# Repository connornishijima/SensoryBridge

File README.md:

https://github.com/connornishijima/SensoryBridge/assets/5051485/211737f4-0c69-49b0-99c4-2fa3d6a7a65e

# SENSORY BRIDGE is **DIFFERENT**

**This isn't the usual "sound-reactive LEDs" you've seen for years.**

**Sensory Bridge is built from the ground up as an open, powerful bridge between sight and sound.** With a show that's reactive to notation, vibrato and more, it produces very unique and pleasant-to-look-at light shows which synchronize to your music without any visible latency. (A built-in MEMS microphone constantly studies what it hears using a special-sauce Goertzel-based Discrete Fourier Transform, at 100 FPS!)

It has to be seen to be believed, *which the video demos below can help with:*

# 

# SENSORY BRIDGE is **SIMPLE**

**Easy controls provide quick access to changing the brightness, color, and smoothing of the display!**

# **KNOBS**

## PHOTONS KNOB

Too bright? *Dim down the show* with the **PHOTONS** knob. The FastLED code in the firmware will use dithering to keep producing color nicely at lower brightness levels.

## CHROMA KNOB

Custom color or automated color based on the music's notation? Choose with the **CHROMA** knob, where turning it all the way to the top enables automated color changes.

## MOOD KNOB

This knob is special. **MOOD** controls *how quickly your LEDs will react to changes in pitch and volume!* A low "mood" will be very soft and gradual, only showing things like the underlying chord progression of a song, whereas a *high* "mood" will be extremely reactive, and can be a little too flashy for some people's liking. Luckily, you can blend the value to anywhere between those two extremes whenever you want to find what look you prefer!

# 

# **BUTTONS**

## NOISE BUTTON

Running the A/C? Is the washing machine suddenly on the spin cycle? Don't worry, just pause the music for a moment and press the **NOISE BUTTON** to run a 3-second calibration to *automagically* have noisy background ambience removed from your light show.

## MODE BUTTON

Sensory Bridge currently has 6 built-in light show modes that you can cycle through:

### "Spectrogram Mode"

This is the default show seen in the videos, based on Discrete Fourier Transform data. Each octave of notation shown on the display has a spectrum of colors for the individual notes, which are lit in sync with your music!

### "Chromagram Mode"

Similar to Spectrogram Mode, but all octaves of notes are rolled into one! Best with the **MOOD** knob at a low to medium setting.

### "Bloom Mode"

This mode differs from the others. The intensity of the audio is shown in the center of the LED strip, and is diffused outward in a non-linear fashion as time passes, leading to a 2001 "Stargate Sequence" effect!. Color is derived from the notes your music is playing.

### "Bloom Mode" (Faster)

Same as above, but double the speed for when you're partying hard!

### "VU Meter Mode"

It's a classic! A bouncing bar graph represents the current loudness of the music.

### "VU Meter Mode (Dot)"

Same as above, but represented with a dot instead of a bar, staying a constant brightness.

## ***MORE MODES WILL BE RELEASED IN FUTURE FIRMWARE UPDATES!***

# 

# **SWEET SPOT**

At the front of the base unit are three LEDs, which indicate if your music is playing too quietly for the auto-ranger to account for, or if it's too loud! (Close to clipping!)

# 

# SENSORY BRIDGE is **FLEXIBLE**

While compatible with any WS2812B or APA102/SK9822-based LED strip (just use the screw terminals at the back!) there's also the option of using the **"Mini Mast"**, a dense strip of 128 1.5mm RGB LEDs on a 260mm long PCB! It just plugs directly into the Sensory Bridge accessory port, making for a very portable solution!

# 

# SENSORY BRIDGE is **OPEN**

--------------------------------------------------------

### NOTE: This repo is used for active development.

For the latest stable release of the Sensory Bridge firmware, **[visit the Releases page](https://github.com/connornishijima/SensoryBridge/releases)**! (Cloning straight from this repo is much like a "nightly" build, and may be broken code!)

--------------------------------------------------------

Powered by an ESP32-S2, Sensory Bridge can be easily reprogrammed for any purpose you'd like! The firmware is [open source](https://github.com/connornishijima/SensoryBridge) under the [MIT License](https://github.com/connornishijima/SensoryBridge/blob/main/LICENSE), so modifying it for your own purposes is quick and easy with the Arduino IDE. You can even download the [board](https://github.com/connornishijima/SensoryBridge/tree/main/extras/OSHW/PCB) and [case STLs](https://github.com/connornishijima/SensoryBridge/tree/main/extras/OSHW/3D%20Printing) to build one yourself!

# 

# WHAT'S **INCLUDED:**

For $50, you'll receive a ***fully assembled Sensory Bridge***, with the latest firmware already installed. For $25 extra, you can have a **Mini Mast** (128 micro-LED PCB, seen above) sent as well, with an accompanying brace that provides rigidity. (It just plugs right into the accessory port on top of Sensory Bridge!)

# EXTRAS YOU **MIGHT NEED:**

## **PAY CLOSE ATTENTION TO THIS SECTION!**

To save on redundant materials you might already own, **your Sensory Bridge does *not* come with the following items:**

- **WS2812B LED Strip** - "144-LEDs per meter" variants are recommended, you can cut the 16 excess LEDs off of the end of the strip or reconfigure your device to interpolate to the 144-LED length at a slightly lower frame rate. ([AMAZON LINK](https://www.amazon.com/WS2812B-Individual-Addressable-144Pixels-Non-Waterproof/dp/B09PBHJG6G/ref=sr_1_5?crid=3KPXUN3NEV06Q&keywords=ws2812b%2Bled%2Bstrip%2B144&qid=1662389723&sprefix=ws2812b%2Bled%2Bstrip%2B144%2Caps%2C128&sr=8-5&th=1))
- **USB-C Cable** ([AMAZON LINK](https://www.amazon.com/JSAUX-Charger-Braided-Compatible-Samsung/dp/B076FPGWNZ/ref=sr_1_9?crid=2YG0J3B874G73&keywords=usb-c+cable&qid=1662388265&sprefix=usb-c+cable%2Caps%2C137&sr=8-9))
- **5V, 2A USB Power Adapter** ([AMAZON LINK](https://www.amazon.com/Certified-Charger-FONKEN-Universal-Compatible/dp/B07DF782WQ/ref=sr_1_4?crid=1WJDP9XHVR3QC&keywords=2a+usb+adapter&qid=1662388344&sprefix=2a+usb+adapter%2Caps%2C131&sr=8-4))
- **Wire Stripper** - If you'd like to use your Sensory Bridge with your own LED strip, you'll either need a wire stripper or strong teeth to get it hooked up neatly! These clamp-style strippers make that process a breeze, so please don't use your teeth: ([AMAZON LINK](https://www.amazon.com/Self-Adjusting-Stripper-Klein-Tools-11061/dp/B00CXKOEQ6/ref=sr_1_5?crid=UIAP8SCLPER3&keywords=wire+strippers&qid=1662390513&sprefix=wire+strippers%2Caps%2C141&sr=8-5))

# 

# FUTURE **PLANS**

Sensory Bridge is going to undergo some upgrades in the following months! You'll be able to easily [update to the latest firmware in minutes with this guide](DEAD LINK).

**Currently planned features are:**

## WiFi Features

Planned for Q1 2023 is a mobile / web app for iOS and Android that will allow users to remotely tweak their display from the couch! This will provide a way to adjust dozens of settings that otherwise couldn't be accessed through just two physical buttons.

## More Lightshow Modes

Currently in development is a system of determining and synchronizing to the BPM of the playing music. Combining this data with the GDFT could mean deducing time signatures, along with musical keys and chord progressions - just another avenue for providing an immersive show!

## Support For Line-In Audio

The accessory port exposes GPIO 17/18 of the ESP32-S2, which are analog inputs. In the future, a PCB can be made to allow Sensory Bridge to use hardwired, passthrough audio via two 3.5mm jacks. This concept does not interfere with the Mini Mast, and the two accessories will be stackable with a modified brace.

# **GETTING STARTED**

The **[GETTING STARTED](https://sensorybridge.rocks/tutorial/) GUIDE** will walk you through the quick-and-easy setup process!

# **DISCLAIMER**

## **Those with [Photosensitive Epilepsy](https://en.wikipedia.org/wiki/Photosensitive_epilepsy) (PSE) should NOT purchase, operate, or otherwise view Sensory Bridge under any condition.**

## **The seller assumes no legal liability for injury caused to persons with PSE that have ignored this warning.**

# **SPONSORS**

- **[mlctrez](https://github.com/mlctrez)**
- **[zxcasd](https://github.com/zxcasd-zxcasd)**

# **CREDITS**

Developed by Connor Nishijima for Lixie Labs (2022)

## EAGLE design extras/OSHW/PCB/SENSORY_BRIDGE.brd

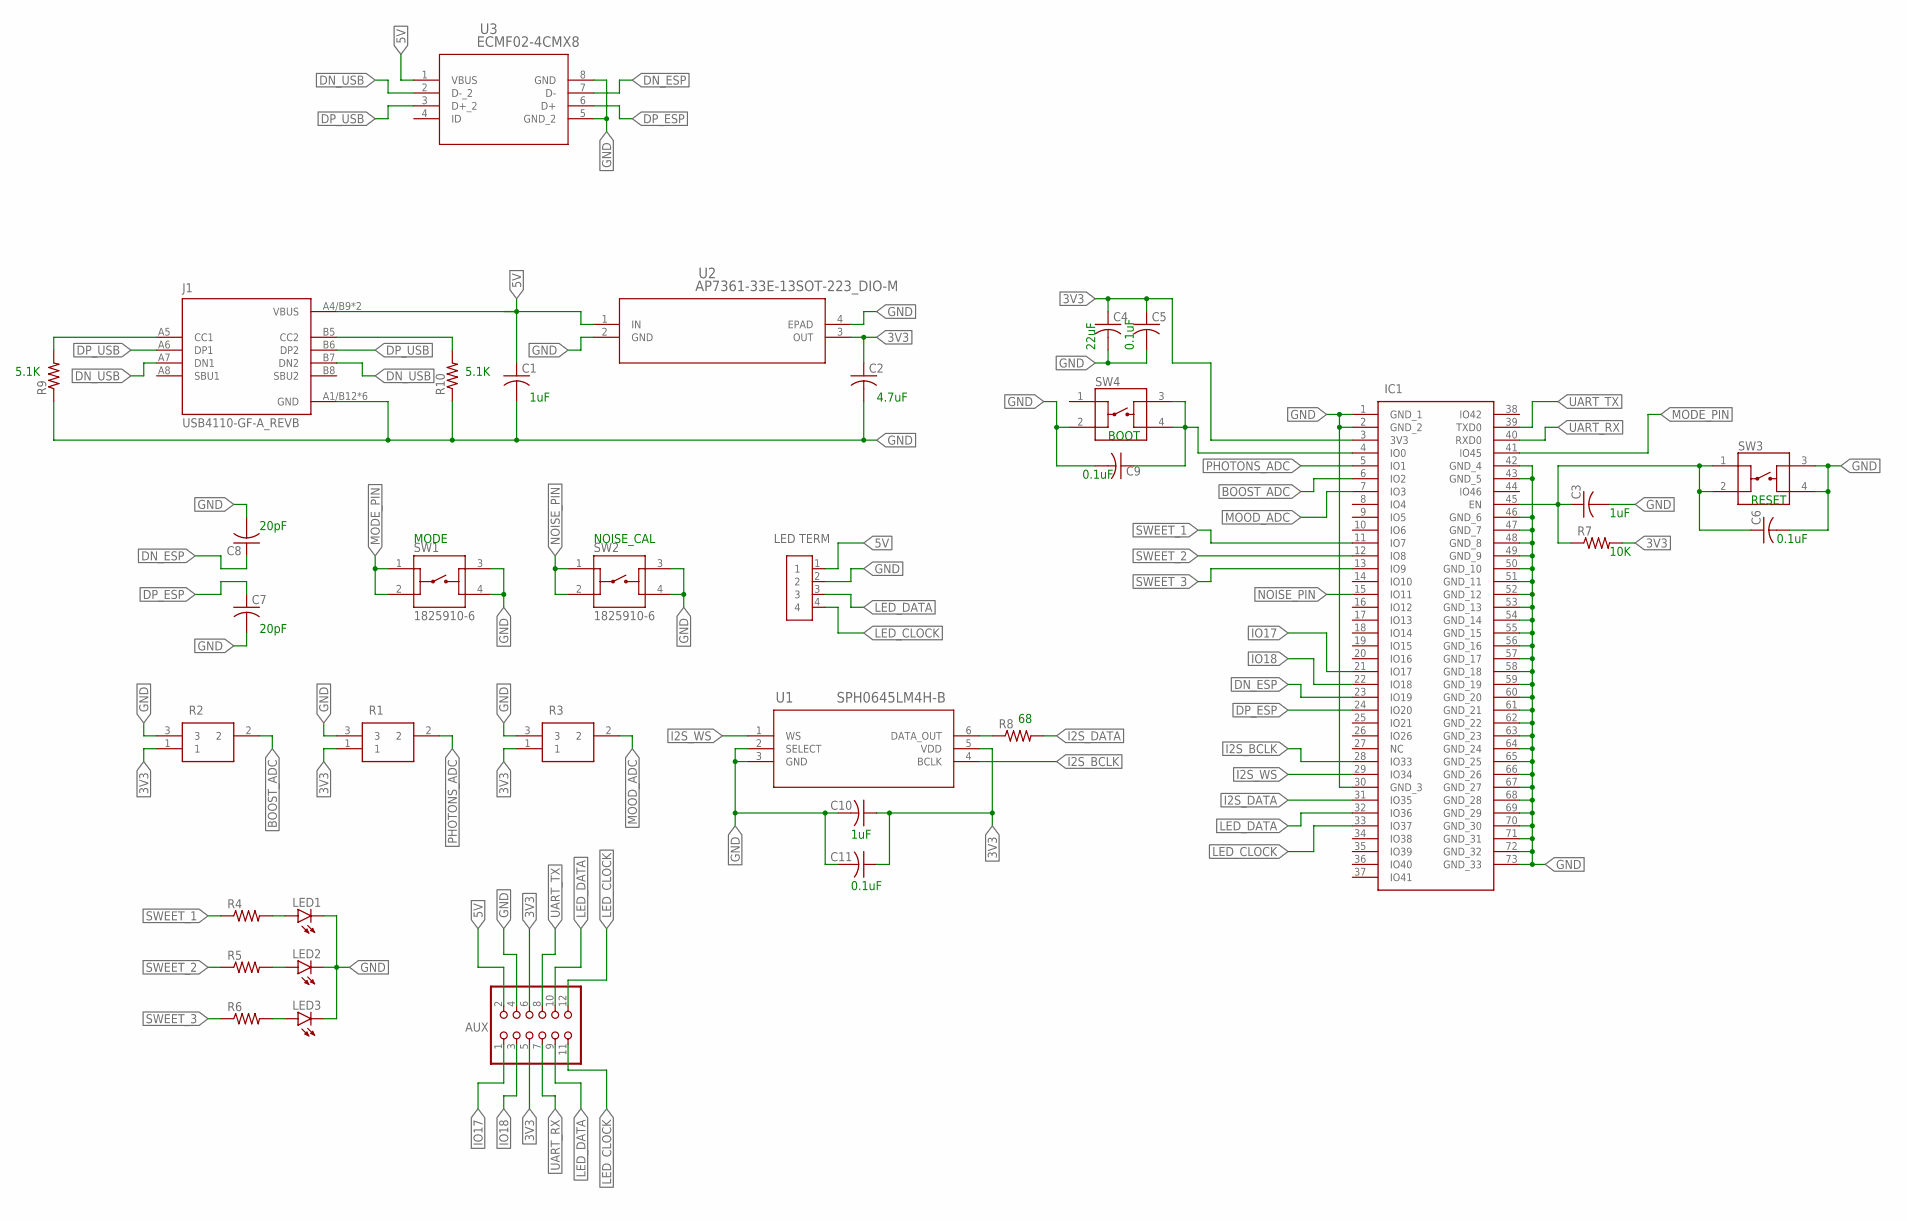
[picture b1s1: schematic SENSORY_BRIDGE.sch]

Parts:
C1, C2, C3, C4, C5, C6, C7, C8, C9, C10, C11: C-USC0805K; C0805K
IC1: ESP32-S2-MINI-1-N4R2; ESP32S2MINI1N4R2
J1: USB4110-GF-A_REVB; GCT_USB4110-GF-A_REVB
J2: 796949-4; TE_796949-4
JP1: PINHD-2X6; 2X06
LED1, LED2, LED3: LED3MM
R1, R2, R3: 3386P-1-103LF; 3386P_1
R4, R5, R6, R7, R8, R9, R10: R-US_R0805; R0805
SW1, SW2: 1825910-6; SW_1825910-6-4
SW3, SW4: PTS525SM15SMTR2LFS; SW_PTS525SM15SMTR2LFS
U1: SPH0645LM4H-B; SPH0645LM4H-B_KNO
U2: AP7361-33E-13SOT-223_DIO-M; SOT-223_DIO-M
U3: ECMF02-4CMX8; MICRO_QFN-8L_STM

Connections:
3V3: C2.1, C4.1, C5.1, C10.1, C11.1, IC1.3 (3V3), JP1.5, JP1.6, R1.1, R2.1, R3.1, R7.2, U1.5 (VDD), U2.3 (OUT)
5V: C1.1, J1.A4/B9 (VBUS), J1.B4/A9 (VBUS), J2.1, JP1.2, U2.1 (IN), U3.1 (VBUS)
BOOST_ADC: IC1.6 (IO2), R2.2
BOOT_LINE: C9.1, IC1.4 (IO0), SW4.3, SW4.4
CC1: J1.A5 (CC1), R9.2
CC2: J1.B5 (CC2), R10.2
DN_ESP: C8.1, IC1.23 (IO19), U3.7 (D-)
DN_USB: J1.A7 (DN1), J1.B7 (DN2), U3.2 (D-_2)
DP_ESP: C7.1, IC1.24 (IO20), U3.6 (D+)
DP_USB: J1.A6 (DP1), J1.B6 (DP2), U3.3 (D+_2)
GND: C1.2, C2.2, C3.2, C4.2, C5.2, C6.2, C7.2, C8.2, C9.2, C10.2, C11.2, IC1.1 (GND_1), IC1.2 (GND_2), IC1.30 (GND_3), IC1.42 (GND_4), IC1.43 (GND_5), IC1.46 (GND_6), IC1.47 (GND_7), IC1.48 (GND_8), IC1.49 (GND_9), IC1.50 (GND_10), IC1.51 (GND_11), IC1.52 (GND_12), IC1.53 (GND_13), IC1.54 (GND_14), IC1.55 (GND_15), IC1.56 (GND_16), IC1.57 (GND_17), IC1.58 (GND_18), IC1.59 (GND_19), IC1.60 (GND_20), IC1.61 (GND_21), IC1.62 (GND_22), IC1.63 (GND_23), IC1.64 (GND_24), IC1.65 (GND_25), IC1.66 (GND_26), IC1.67 (GND_27), IC1.68 (GND_28), IC1.69 (GND_29), IC1.70 (GND_30), IC1.71 (GND_31), IC1.72 (GND_32), IC1.73 (GND_33), J1.A1/B12 (GND), J1.B1/A12 (GND), J1.S1 (GND), J1.S2 (GND), J1.S3 (GND), J1.S4 (GND), J2.2, JP1.4, LED1.K (C), LED2.K (C), LED3.K (C), R1.3, R2.3, R3.3, R9.1, R10.1, SW1.3, SW1.4, SW2.3, SW2.4, SW3.3, SW3.4, SW4.2, U1.2 (SELECT), U1.3 (GND), U2.2 (GND), U2.4 (EPAD), U3.5 (GND_2), U3.8 (GND)
I2S_BCLK: IC1.28 (IO33), U1.4 (BCLK)
I2S_DATA: IC1.31 (IO35), R8.2
I2S_WS: IC1.29 (IO34), U1.1 (WS)
IO17: IC1.21 (IO17), JP1.1
IO18: IC1.22 (IO18), JP1.3
LED_CLOCK: IC1.33 (IO37), J2.4, JP1.11, JP1.12
LED_DATA: IC1.32 (IO36), J2.3, JP1.9, JP1.10
MODE_PIN: IC1.41 (IO45), SW1.1, SW1.2
MOOD_ADC: IC1.7 (IO3), R3.2
unnamed: R8.1, U1.6 (DATA_OUT)
unnamed: LED1.A, R4.2
unnamed: LED2.A, R5.2
unnamed: LED3.A, R6.2
NOISE_PIN: IC1.15 (IO11), SW2.1, SW2.2
PHOTONS_ADC: IC1.5 (IO1), R1.2
RESET_LINE: C3.1, C6.1, IC1.45 (EN), R7.1, SW3.1, SW3.2
SWEET_1: IC1.11 (IO7), R4.1
SWEET_2: IC1.12 (IO8), R5.1
SWEET_3: IC1.13 (IO9), R6.1
UART_RX: IC1.40 (RXD0), JP1.7
UART_TX: IC1.39 (TXD0), JP1.8

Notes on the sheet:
1uF
4.7uF
10K
22uF
0.1uF
BOOT
RESET
20pF
NOISE_CAL
MODE
5.1K
LED TERM
AUX

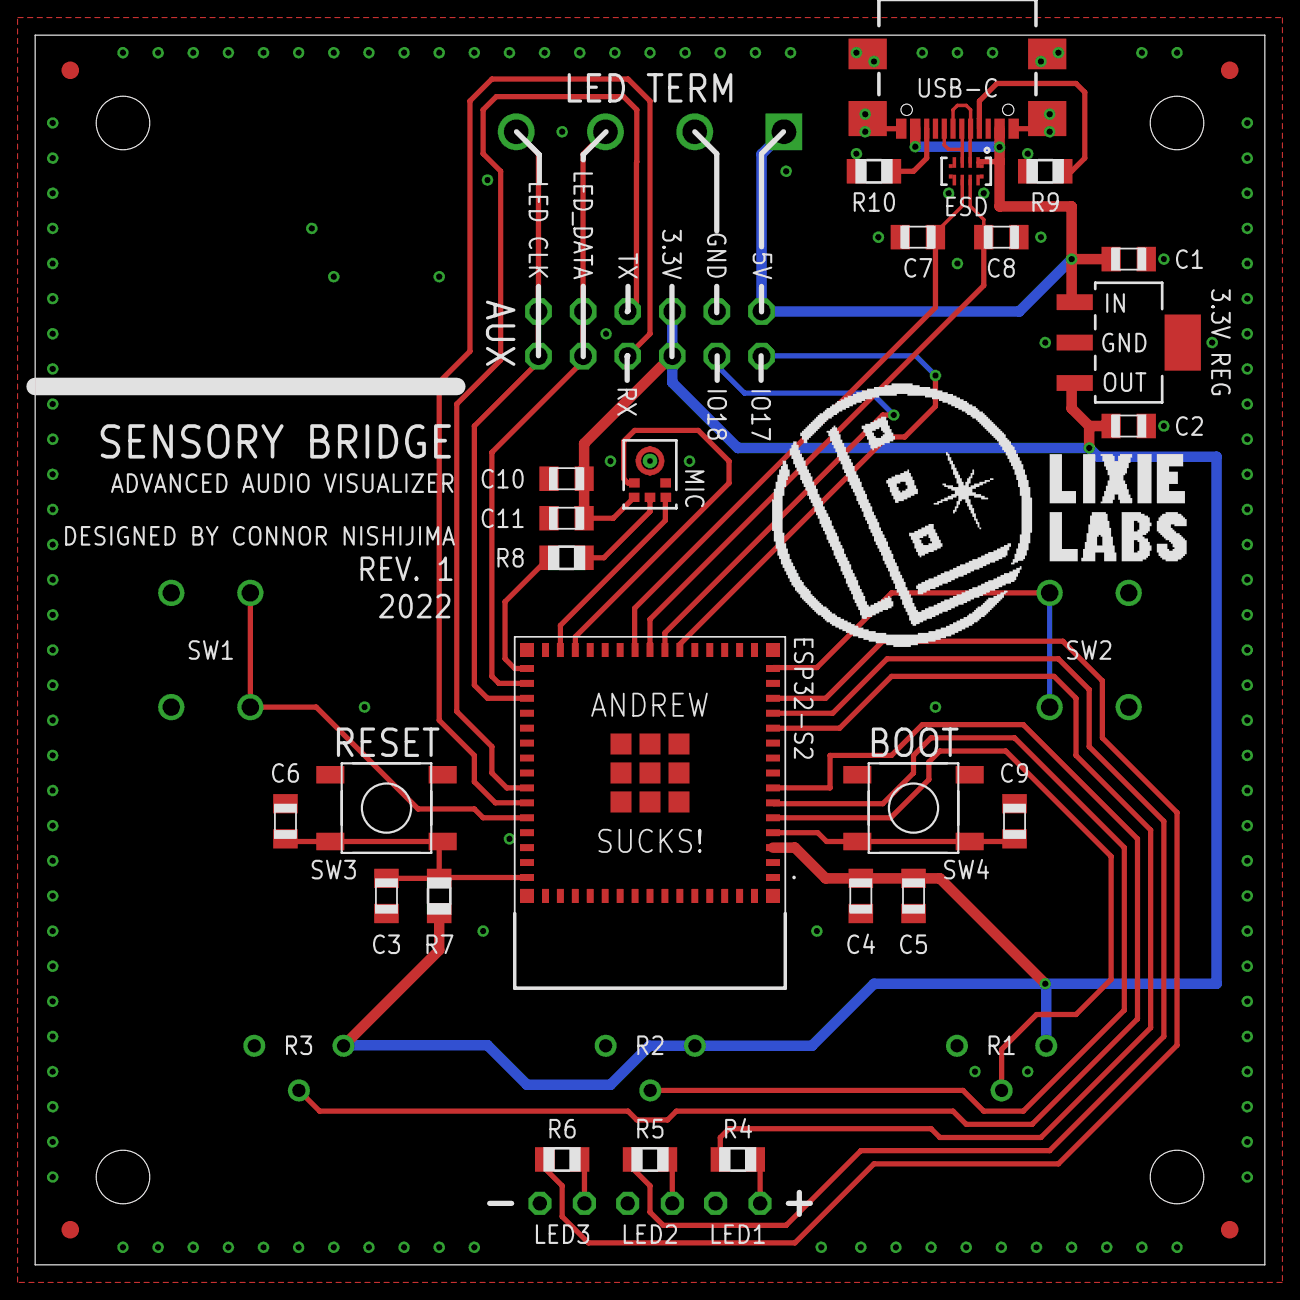
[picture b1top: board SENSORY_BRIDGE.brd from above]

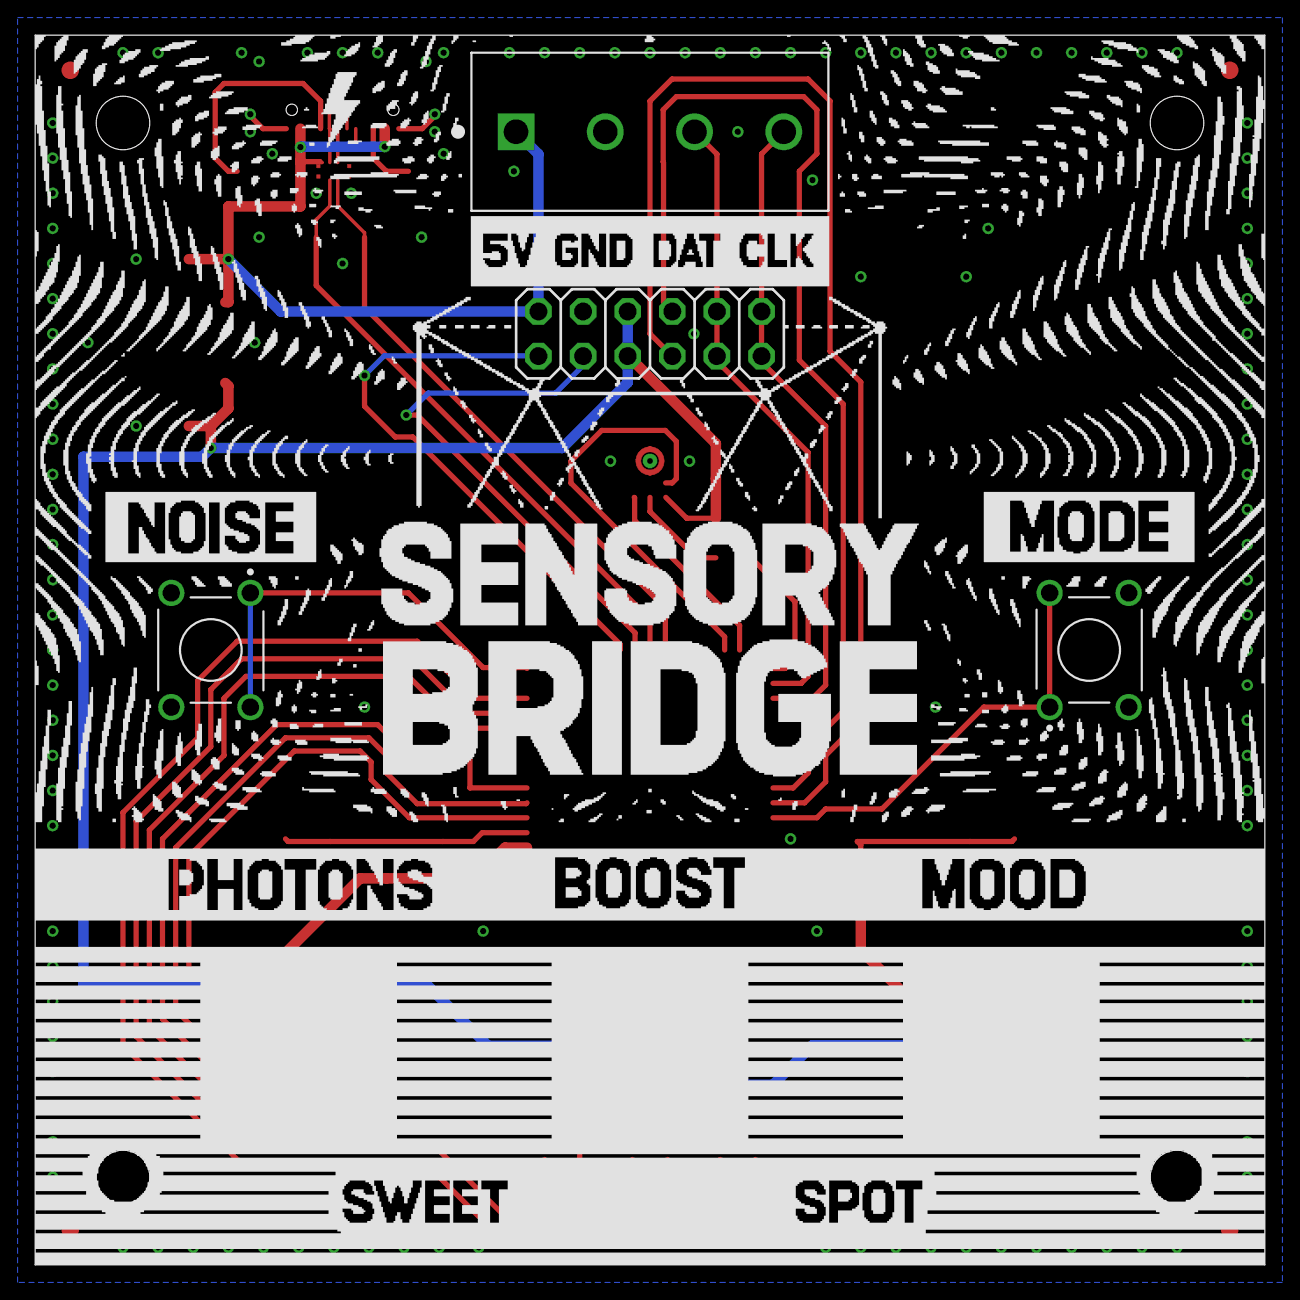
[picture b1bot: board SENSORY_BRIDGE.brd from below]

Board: 2 copper layers, 70.0 x 70.0 mm, 39 parts (10 on the bottom side), 32 nets.

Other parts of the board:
U$1, U$2, U$3, U$4: CIRCLE-1MM-2R

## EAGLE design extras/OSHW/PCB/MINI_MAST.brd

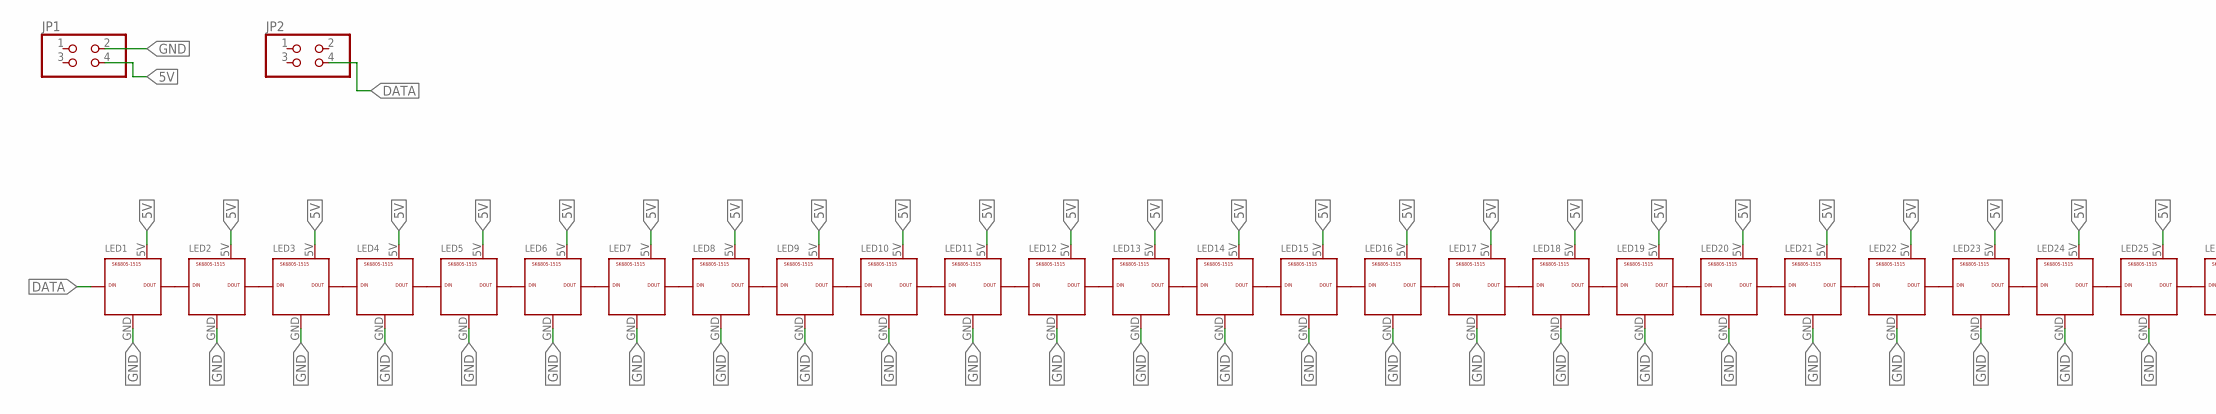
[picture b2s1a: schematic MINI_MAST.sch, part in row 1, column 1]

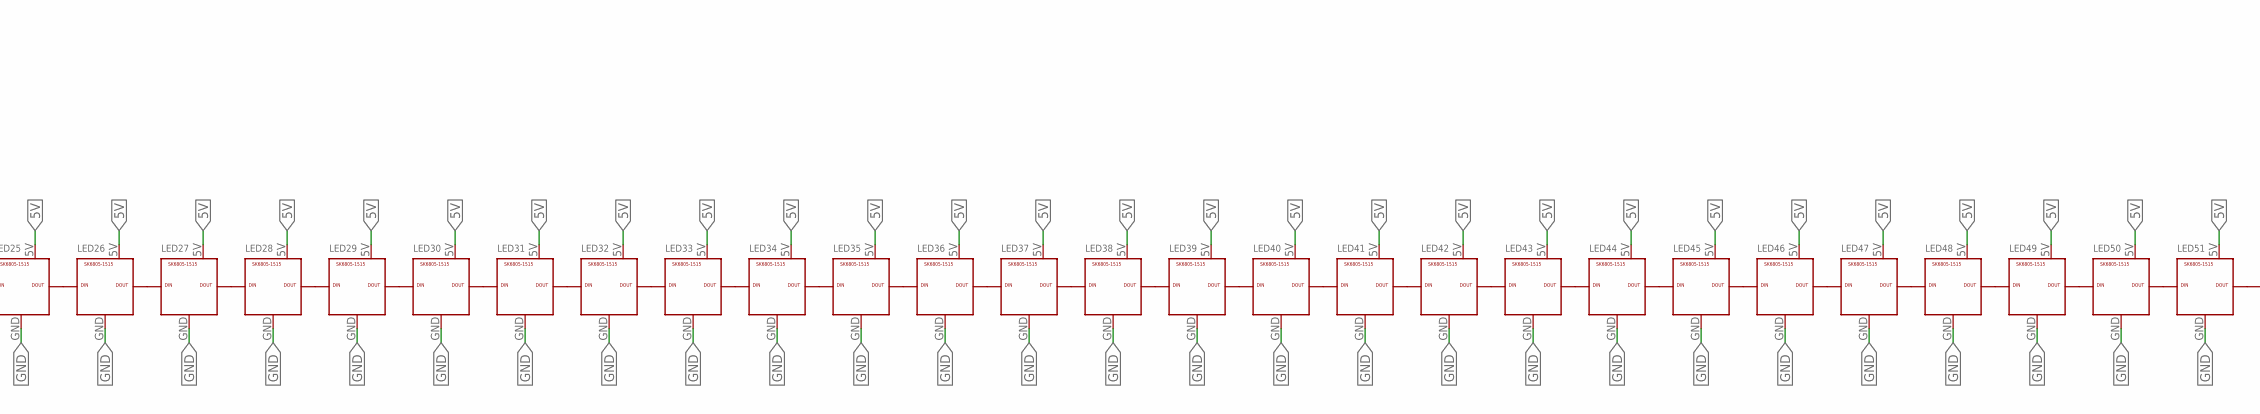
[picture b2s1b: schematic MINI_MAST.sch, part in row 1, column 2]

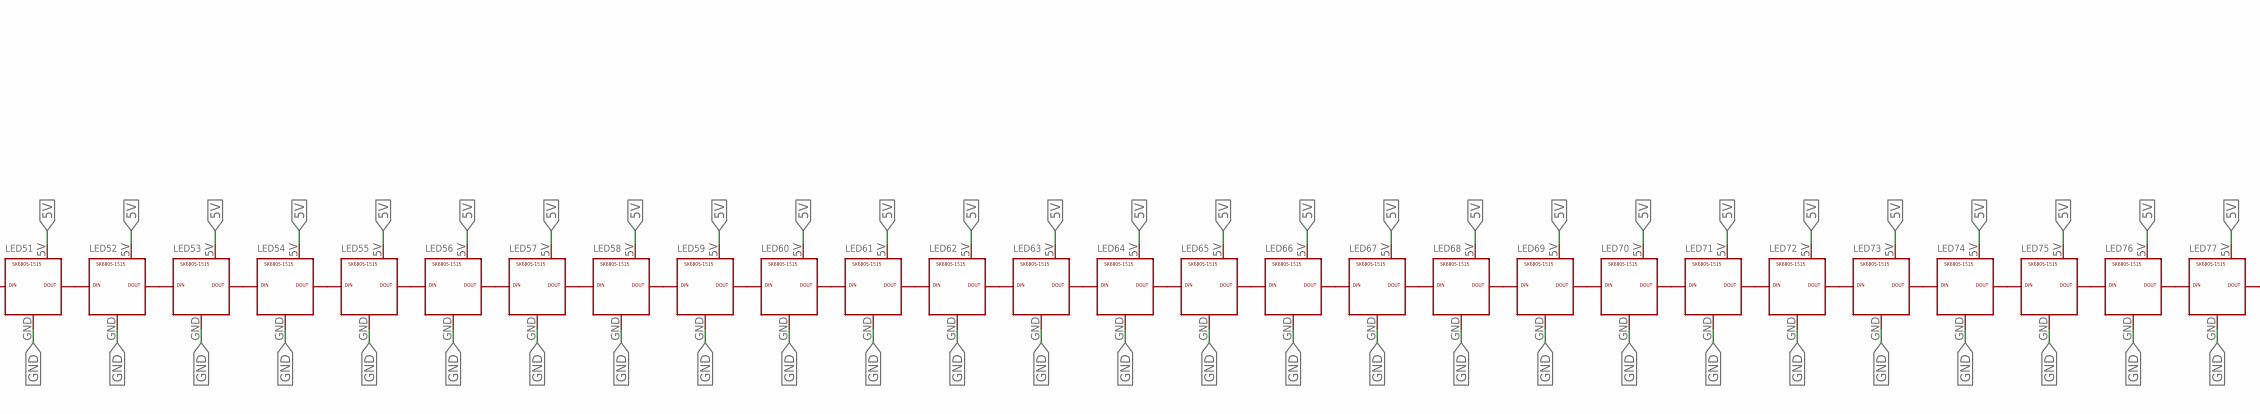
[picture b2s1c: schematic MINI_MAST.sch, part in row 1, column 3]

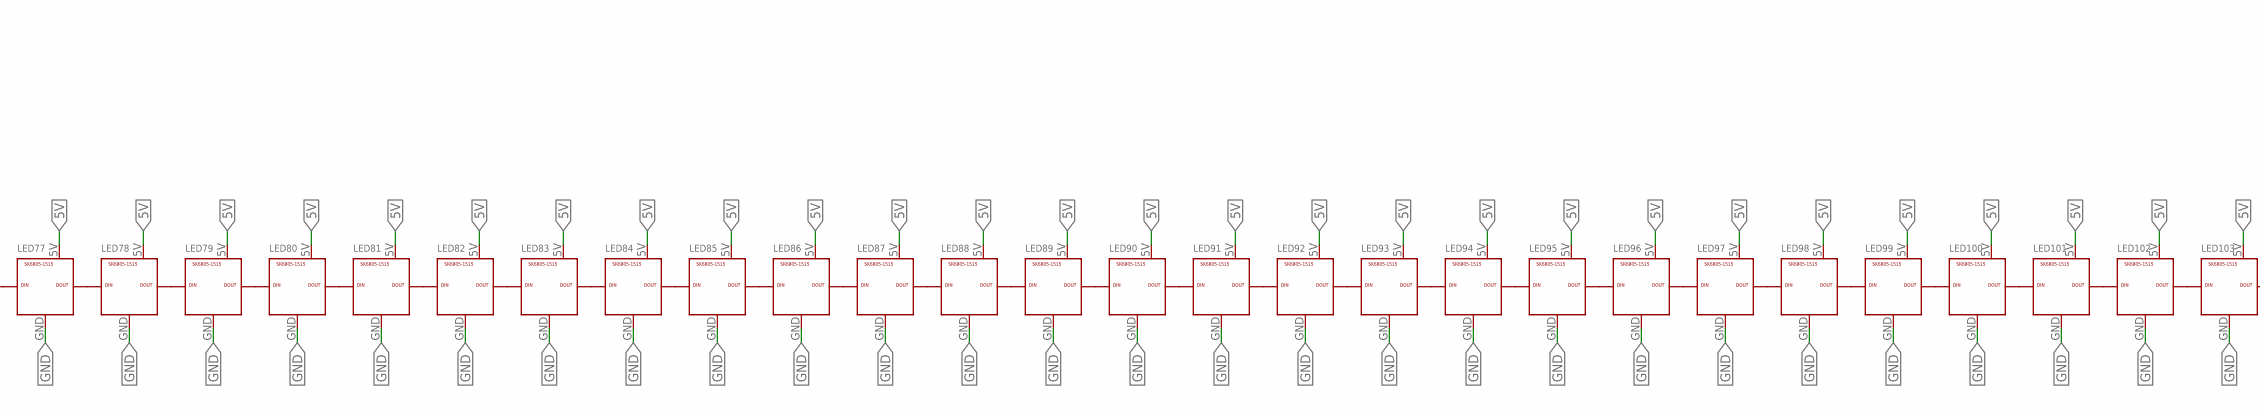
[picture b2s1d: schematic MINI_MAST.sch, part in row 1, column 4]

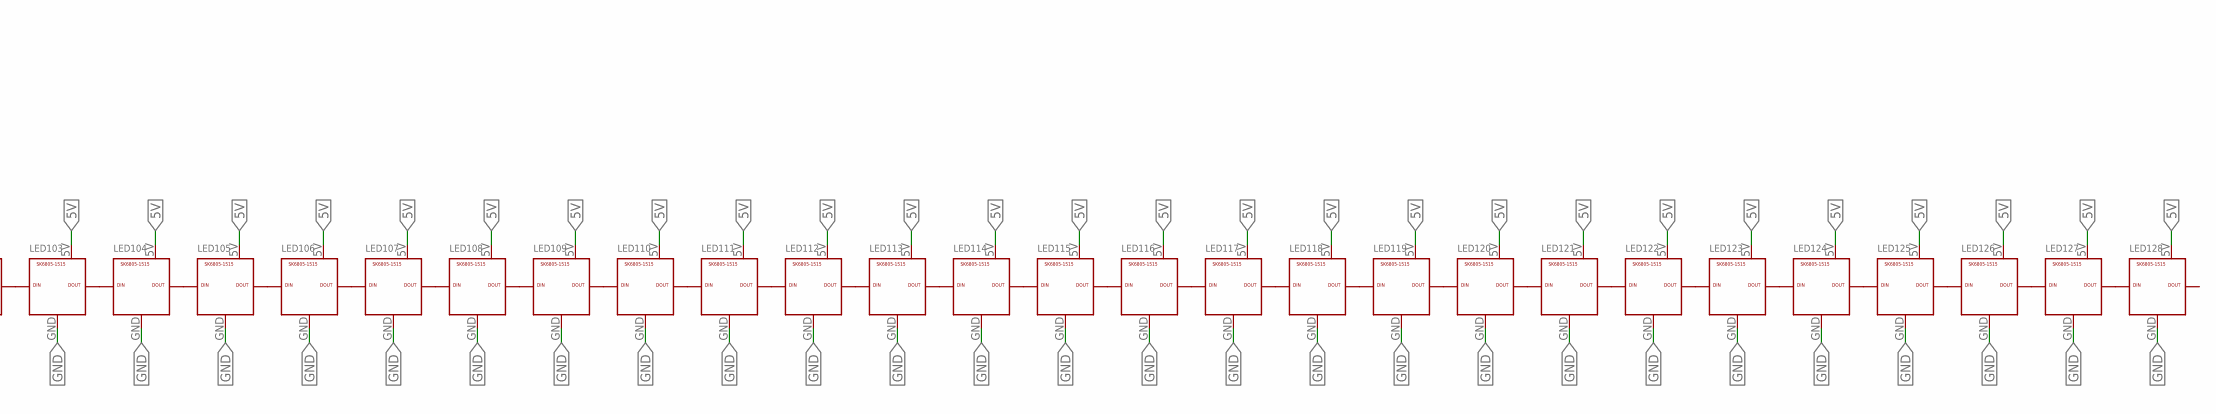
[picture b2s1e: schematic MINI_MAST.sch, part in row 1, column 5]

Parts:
JP1, JP2: PINHD-2X2/90; 2X02/90
LED1, LED2, LED3, LED4, LED5, LED6, LED7, LED8, LED9, LED10, LED11, LED12, LED13, LED14, LED15, LED16, LED17, LED18, LED19, LED20, LED21, LED22, LED23, LED24, LED25, LED26, LED27, LED28, LED29, LED30, LED31, LED32, LED33, LED34, LED35, LED36, LED37, LED38, LED39, LED40, LED41, LED42, LED43, LED44, LED45, LED46, LED47, LED48, LED49, LED50, LED51, LED52, LED53, LED54, LED55, LED56, LED57, LED58, LED59, LED60, LED61, LED62, LED63, LED64, LED65, LED66, LED67, LED68, LED69, LED70, LED71, LED72, LED73, LED74, LED75, LED76, LED77, LED78, LED79, LED80, LED81, LED82, LED83, LED84, LED85, LED86, LED87, LED88, LED89, LED90, LED91, LED92, LED93, LED94, LED95, LED96, LED97, LED98, LED99, LED100, LED101, LED102, LED103, LED104, LED105, LED106, LED107, LED108, LED109, LED110, LED111, LED112, LED113, LED114, LED115, LED116, LED117, LED118, LED119, LED120, LED121, LED122, LED123, LED124, LED125, LED126, LED127, LED128: SK6805-1515; 1515

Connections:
5V: JP1.4, LED1.5V, LED2.5V, LED3.5V, LED4.5V, LED5.5V, LED6.5V, LED7.5V, LED8.5V, LED9.5V, LED10.5V, LED11.5V, LED12.5V, LED13.5V, LED14.5V, LED15.5V, LED16.5V, LED17.5V, LED18.5V, LED19.5V, LED20.5V, LED21.5V, LED22.5V, LED23.5V, LED24.5V, LED25.5V, LED26.5V, LED27.5V, LED28.5V, LED29.5V, LED30.5V, LED31.5V, LED32.5V, LED33.5V, LED34.5V, LED35.5V, LED36.5V, LED37.5V, LED38.5V, LED39.5V, LED40.5V, LED41.5V, LED42.5V, LED43.5V, LED44.5V, LED45.5V, LED46.5V, LED47.5V, LED48.5V, LED49.5V, LED50.5V, LED51.5V, LED52.5V, LED53.5V, LED54.5V, LED55.5V, LED56.5V, LED57.5V, LED58.5V, LED59.5V, LED60.5V, LED61.5V, LED62.5V, LED63.5V, LED64.5V, LED65.5V, LED66.5V, LED67.5V, LED68.5V, LED69.5V, LED70.5V, LED71.5V, LED72.5V, LED73.5V, LED74.5V, LED75.5V, LED76.5V, LED77.5V, LED78.5V, LED79.5V, LED80.5V, LED81.5V, LED82.5V, LED83.5V, LED84.5V, LED85.5V, LED86.5V, LED87.5V, LED88.5V, LED89.5V, LED90.5V, LED91.5V, LED92.5V, LED93.5V, LED94.5V, LED95.5V, LED96.5V, LED97.5V, LED98.5V, LED99.5V, LED100.5V, LED101.5V, LED102.5V, LED103.5V, LED104.5V, LED105.5V, LED106.5V, LED107.5V, LED108.5V, LED109.5V, LED110.5V, LED111.5V, LED112.5V, LED113.5V, LED114.5V, LED115.5V, LED116.5V, LED117.5V, LED118.5V, LED119.5V, LED120.5V, LED121.5V, LED122.5V, LED123.5V, LED124.5V, LED125.5V, LED126.5V, LED127.5V, LED128.5V
DATA: JP2.4, LED1.DIN
DATA1: LED8.DOUT, LED9.DIN
DATA2: LED24.DOUT, LED25.DIN
DATA3: LED40.DOUT, LED41.DIN
DATA4: LED56.DOUT, LED57.DIN
DATA5: LED64.DOUT, LED65.DIN
DATA6: LED72.DOUT, LED73.DIN
DATA7: LED88.DOUT, LED89.DIN
DATA8: LED104.DOUT, LED105.DIN
DATA9: LED120.DOUT, LED121.DIN
GND: JP1.2, LED1.GND, LED2.GND, LED3.GND, LED4.GND, LED5.GND, LED6.GND, LED7.GND, LED8.GND, LED9.GND, LED10.GND, LED11.GND, LED12.GND, LED13.GND, LED14.GND, LED15.GND, LED16.GND, LED17.GND, LED18.GND, LED19.GND, LED20.GND, LED21.GND, LED22.GND, LED23.GND, LED24.GND, LED25.GND, LED26.GND, LED27.GND, LED28.GND, LED29.GND, LED30.GND, LED31.GND, LED32.GND, LED33.GND, LED34.GND, LED35.GND, LED36.GND, LED37.GND, LED38.GND, LED39.GND, LED40.GND, LED41.GND, LED42.GND, LED43.GND, LED44.GND, LED45.GND, LED46.GND, LED47.GND, LED48.GND, LED49.GND, LED50.GND, LED51.GND, LED52.GND, LED53.GND, LED54.GND, LED55.GND, LED56.GND, LED57.GND, LED58.GND, LED59.GND, LED60.GND, LED61.GND, LED62.GND, LED63.GND, LED64.GND, LED65.GND, LED66.GND, LED67.GND, LED68.GND, LED69.GND, LED70.GND, LED71.GND, LED72.GND, LED73.GND, LED74.GND, LED75.GND, LED76.GND, LED77.GND, LED78.GND, LED79.GND, LED80.GND, LED81.GND, LED82.GND, LED83.GND, LED84.GND, LED85.GND, LED86.GND, LED87.GND, LED88.GND, LED89.GND, LED90.GND, LED91.GND, LED92.GND, LED93.GND, LED94.GND, LED95.GND, LED96.GND, LED97.GND, LED98.GND, LED99.GND, LED100.GND, LED101.GND, LED102.GND, LED103.GND, LED104.GND, LED105.GND, LED106.GND, LED107.GND, LED108.GND, LED109.GND, LED110.GND, LED111.GND, LED112.GND, LED113.GND, LED114.GND, LED115.GND, LED116.GND, LED117.GND, LED118.GND, LED119.GND, LED120.GND, LED121.GND, LED122.GND, LED123.GND, LED124.GND, LED125.GND, LED126.GND, LED127.GND, LED128.GND
unnamed: LED1.DOUT, LED2.DIN
unnamed: LED3.DOUT, LED4.DIN
unnamed: LED2.DOUT, LED3.DIN
unnamed: LED5.DOUT, LED6.DIN
unnamed: LED7.DOUT, LED8.DIN
unnamed: LED6.DOUT, LED7.DIN
unnamed: LED4.DOUT, LED5.DIN
unnamed: LED9.DOUT, LED10.DIN
unnamed: LED11.DOUT, LED12.DIN
unnamed: LED10.DOUT, LED11.DIN
unnamed: LED13.DOUT, LED14.DIN
unnamed: LED15.DOUT, LED16.DIN
unnamed: LED14.DOUT, LED15.DIN
unnamed: LED12.DOUT, LED13.DIN
unnamed: LED17.DOUT, LED18.DIN
unnamed: LED19.DOUT, LED20.DIN
unnamed: LED18.DOUT, LED19.DIN
unnamed: LED21.DOUT, LED22.DIN
unnamed: LED23.DOUT, LED24.DIN
unnamed: LED22.DOUT, LED23.DIN
unnamed: LED20.DOUT, LED21.DIN
unnamed: LED25.DOUT, LED26.DIN
unnamed: LED27.DOUT, LED28.DIN
unnamed: LED26.DOUT, LED27.DIN
unnamed: LED29.DOUT, LED30.DIN
unnamed: LED31.DOUT, LED32.DIN
unnamed: LED30.DOUT, LED31.DIN
unnamed: LED28.DOUT, LED29.DIN
unnamed: LED16.DOUT, LED17.DIN
unnamed: LED33.DOUT, LED34.DIN
unnamed: LED35.DOUT, LED36.DIN
unnamed: LED34.DOUT, LED35.DIN
unnamed: LED37.DOUT, LED38.DIN
unnamed: LED39.DOUT, LED40.DIN
unnamed: LED38.DOUT, LED39.DIN
unnamed: LED36.DOUT, LED37.DIN
unnamed: LED41.DOUT, LED42.DIN
unnamed: LED43.DOUT, LED44.DIN
unnamed: LED42.DOUT, LED43.DIN
unnamed: LED45.DOUT, LED46.DIN
unnamed: LED47.DOUT, LED48.DIN
unnamed: LED46.DOUT, LED47.DIN
unnamed: LED44.DOUT, LED45.DIN
unnamed: LED49.DOUT, LED50.DIN
unnamed: LED51.DOUT, LED52.DIN
unnamed: LED50.DOUT, LED51.DIN
unnamed: LED53.DOUT, LED54.DIN
unnamed: LED55.DOUT, LED56.DIN
unnamed: LED54.DOUT, LED55.DIN
unnamed: LED52.DOUT, LED53.DIN
unnamed: LED57.DOUT, LED58.DIN
unnamed: LED59.DOUT, LED60.DIN
unnamed: LED58.DOUT, LED59.DIN
unnamed: LED61.DOUT, LED62.DIN
unnamed: LED63.DOUT, LED64.DIN
unnamed: LED62.DOUT, LED63.DIN
unnamed: LED60.DOUT, LED61.DIN
unnamed: LED48.DOUT, LED49.DIN
unnamed: LED32.DOUT, LED33.DIN
unnamed: LED65.DOUT, LED66.DIN
unnamed: LED67.DOUT, LED68.DIN
unnamed: LED66.DOUT, LED67.DIN
unnamed: LED69.DOUT, LED70.DIN
unnamed: LED71.DOUT, LED72.DIN
unnamed: LED70.DOUT, LED71.DIN
unnamed: LED68.DOUT, LED69.DIN
unnamed: LED73.DOUT, LED74.DIN
unnamed: LED75.DOUT, LED76.DIN
unnamed: LED74.DOUT, LED75.DIN
unnamed: LED77.DOUT, LED78.DIN
unnamed: LED79.DOUT, LED80.DIN
unnamed: LED78.DOUT, LED79.DIN
unnamed: LED76.DOUT, LED77.DIN
unnamed: LED81.DOUT, LED82.DIN
unnamed: LED83.DOUT, LED84.DIN
unnamed: LED82.DOUT, LED83.DIN
unnamed: LED85.DOUT, LED86.DIN
unnamed: LED87.DOUT, LED88.DIN
unnamed: LED86.DOUT, LED87.DIN
unnamed: LED84.DOUT, LED85.DIN
unnamed: LED89.DOUT, LED90.DIN
unnamed: LED91.DOUT, LED92.DIN
unnamed: LED90.DOUT, LED91.DIN
unnamed: LED93.DOUT, LED94.DIN
unnamed: LED95.DOUT, LED96.DIN
unnamed: LED94.DOUT, LED95.DIN
unnamed: LED92.DOUT, LED93.DIN
unnamed: LED80.DOUT, LED81.DIN
unnamed: LED97.DOUT, LED98.DIN
unnamed: LED99.DOUT, LED100.DIN
unnamed: LED98.DOUT, LED99.DIN
unnamed: LED101.DOUT, LED102.DIN
unnamed: LED103.DOUT, LED104.DIN
unnamed: LED102.DOUT, LED103.DIN
unnamed: LED100.DOUT, LED101.DIN
unnamed: LED105.DOUT, LED106.DIN
unnamed: LED107.DOUT, LED108.DIN
unnamed: LED106.DOUT, LED107.DIN
unnamed: LED109.DOUT, LED110.DIN
unnamed: LED111.DOUT, LED112.DIN
unnamed: LED110.DOUT, LED111.DIN
unnamed: LED108.DOUT, LED109.DIN
unnamed: LED113.DOUT, LED114.DIN
unnamed: LED115.DOUT, LED116.DIN
unnamed: LED114.DOUT, LED115.DIN
unnamed: LED117.DOUT, LED118.DIN
unnamed: LED119.DOUT, LED120.DIN
unnamed: LED118.DOUT, LED119.DIN
unnamed: LED116.DOUT, LED117.DIN
unnamed: LED121.DOUT, LED122.DIN
unnamed: LED123.DOUT, LED124.DIN
unnamed: LED122.DOUT, LED123.DIN
unnamed: LED125.DOUT, LED126.DIN
unnamed: LED127.DOUT, LED128.DIN
unnamed: LED126.DOUT, LED127.DIN
unnamed: LED124.DOUT, LED125.DIN
unnamed: LED112.DOUT, LED113.DIN
unnamed: LED96.DOUT, LED97.DIN

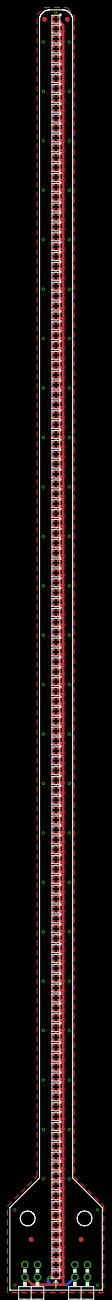
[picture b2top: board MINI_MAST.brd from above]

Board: 2 copper layers, 18.7 x 259.0 mm, 134 parts (0 on the bottom side), 130 nets.

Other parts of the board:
U$1, U$2, U$3, U$4: CIRCLE-1MM-2R

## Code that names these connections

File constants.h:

#define SAMPLE_RATE  18750
#define BUFFER_SIZE  256
#define I2S_PORT     I2S_NUM_0

#define FFT_HISTORY_LEN            6
#define AMBIENT_NOISE_SAMPLES      128

#define SWEET_SPOT   0.75F

#define PHOTONS_PIN  1
#define BOOST_PIN    2
#define MOOD_PIN     3

#define SWEET_SPOT_LEFT_PIN    7
#define SWEET_SPOT_CENTER_PIN  8
#define SWEET_SPOT_RIGHT_PIN   9

#define NOISE_CAL_PIN  11
#define MODE_PIN       45

#define NUM_LEDS       128
#define LED_DATA_PIN   36
#define LED_CLOCK_PIN  37

#define I2S_BCLK_PIN   33
#define I2S_LRCLK_PIN  34
#define I2S_DOUT_PIN   35

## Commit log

2022-09-04 RC1 Update
2022-09-04 Added images
2022-09-05 Added demo images
2022-09-05 Added OSHW
2022-09-05 Added OSHW files
2022-09-09 Pre-ship refinements
2022-09-11 Final 1.0.0 Changes
2022-09-11 File cleanup
2022-09-22 1.1.0 Update
2022-09-22 Folder Structure Fix
2022-09-22 Moved LICENSE
2022-09-23 [ImgBot] Optimize images
    *Total -- 1,727.24kb -> 1,597.01kb (7.54%)
    /extras/img/firmware_settings.png -- 48.82kb -> 16.23kb (66.76%)
    /extras/img/oshw_facts.svg -- 8.76kb -> 7.53kb (13.99%)
    /extras/img/2.jpg -- 239.88kb -> 218.03kb (9.11%)
    /extras/img/6.jpg -- 194.99kb -> 183.08kb (6.11%)
    /extras/img/12.jpg -- 236.11kb -> 222.35kb (5.83%)
2022-10-03 Initial Color Palette work
2022-10-03 Tweaks
2022-10-04 Update fft.h per connornishijima/SensoryBridge#9
2022-10-07 Added USB PID code
    Cool, cool cool cool
2022-10-07 Documentation Update
2022-10-07 Format Cleanup
2022-10-07 Documentation / cleanup
2022-10-07 Cleanup
2022-10-07 Updated sponsor list
2022-10-07 Fixed LED definition to be more flexible with color ordering
2022-10-10 First WiFi features, FFT tweaks
2022-11-17 Firmware 2.0.0 Upload
2022-11-17 Added new titles and fixed .ino name
2022-11-20 RNG pin/DotStar fix
2022-11-20 @mlctrez fixes
    Thanks man!
2023-01-09 Initial 3.0.0 upload (Only working on ESP32-S3 at this time)
2023-01-16 3.0.0 Open Beta!
    Definitely not fully working, not a stable release yet.
2023-01-18 3.0.0-beta2 Update!
2023-01-19 3.0.0-beta3 upload
2023-01-21 3.0.0-beta4 upload
2023-01-21 Removed reference to deprecated CONFIG.WAVEFORM_NOISE_FLOOR
2023-01-23 3.0.0-beta5 upload
2023-01-25 Added settings page imagery
2023-01-25 [ImgBot] Optimize images
    *Total -- 3,085.27kb -> 2,886.52kb (6.44%)
    /extras/img/17.png -- 385.08kb -> 327.07kb (15.06%)
    /extras/img/8.jpg -- 192.55kb -> 178.40kb (7.35%)
    /extras/img/1.jpg -- 182.20kb -> 169.63kb (6.9%)
    /extras/img/5.jpg -- 174.00kb -> 163.66kb (5.94%)
    /extras/img/15.jpg -- 299.04kb -> 281.43kb (5.89%)
2023-01-25 3.0.0 Firmware Update!
    Woohoo! See the Releases page
2023-01-25 Vastly dropped Sweet Spot brightness for better night-time usage
2023-01-25 Added option to reverse LED order for upside-down strips
2023-01-25 Added 3.0.0 required Arduino settings image
2023-01-25 Fixed image and added arrows
2023-01-26 3.0.1 upload
2023-01-29 [ImgBot] Optimize images
    *Total -- 384.14kb -> 345.70kb (10.01%)
    /extras/img/firmware_settings_300.png -- 44.75kb -> 21.57kb (51.79%)
    /extras/img/3.jpg -- 339.38kb -> 324.13kb (4.49%)
2023-01-30 3.1.0 Upload
2023-02-08 Added Modem Mode via NOISE button on boot
2023-05-08 3.2.0 Update
2023-07-11 4.0.0 Initial Upload
    WOOHOO!
    See the Releases page for the changelog!
2023-08-06 all updates for the LumosStick
2023-08-07 tested with LumosRing
2023-10-02 Found potential cause of "stuck green LED"
2024-02-09 Update LICENSE
2024-03-21 Potential "stuck Microdose" fix
2024-03-21 Increase GPU thread stack size
2024-03-21 Added FreeRTOS vTaskDelay(1) to LED thread

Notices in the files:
parts and their libraries:
COPYRIGHT: Copyright (C) 2022 Ultra Librarian. All rights reserved.
